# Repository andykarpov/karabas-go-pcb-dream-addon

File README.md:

# Karabas-Go rev.A SAM2695 addon

A small pcb to add midi functionality to Karabas-Go (and possibly other ZX Spectrum machines with AY chip).

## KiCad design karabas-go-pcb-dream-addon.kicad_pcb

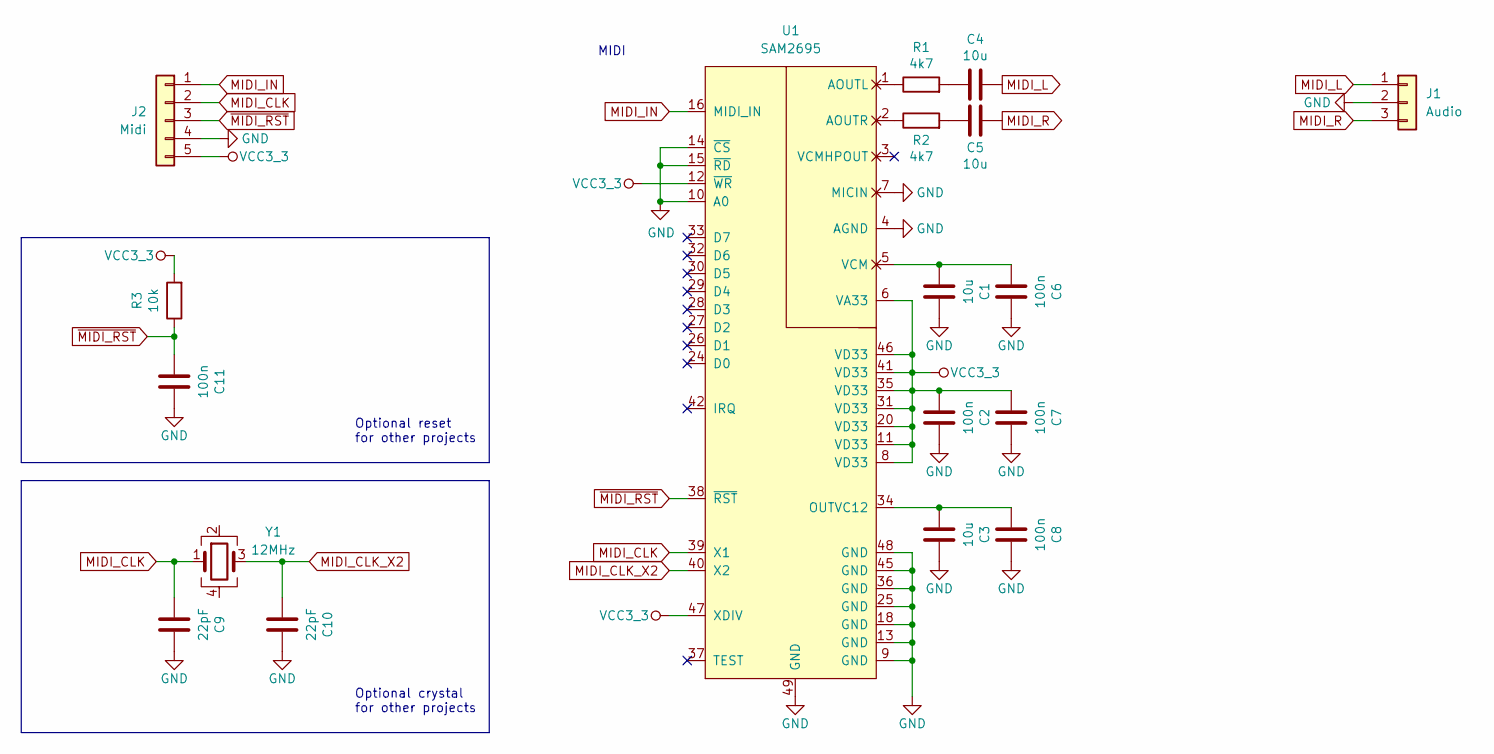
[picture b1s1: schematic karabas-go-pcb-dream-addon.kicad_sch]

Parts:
C1, C3, C4, C5: 10u; C_0603_1608Metric_Pad1.08x0.95mm_HandSolder
C2, C6, C7, C8, C11: 100n; C_0603_1608Metric_Pad1.08x0.95mm_HandSolder
C9, C10: 22pF; C_0603_1608Metric_Pad1.08x0.95mm_HandSolder
J1: Audio; PinHeader_1x03_P2.54mm_Vertical
J2: Midi; PinHeader_1x05_P2.54mm_Vertical
R1, R2: 4k7; R_0603_1608Metric_Pad0.98x0.95mm_HandSolder
R3: 10k; R_0603_1608Metric_Pad0.98x0.95mm_HandSolder
U1: SAM2695; QFN-48-1EP_6x6mm_P0.4mm_EP4.2x4.2mm
Y1: 12MHz; Crystal_SMD_3225-4Pin_3.2x2.5mm_HandSoldering

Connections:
GND: C1.2, C2.2, C3.2, C6.2, C7.2, C8.2, C9.2, C10.2, C11.2, J1.2, J2.4, U1.4 (AGND), U1.7 (MICIN), U1.9 (GND), U1.10 (A0), U1.13 (GND), U1.14 (~CS), U1.15 (~RD), U1.18 (GND), U1.25 (GND), U1.36 (GND), U1.45 (GND), U1.48 (GND), U1.49 (GND)
MIDI_CLK: C9.1, J2.2, U1.39 (X1), Y1.1
MIDI_CLK_X2: C10.1, U1.40 (X2), Y1.3
MIDI_IN: J2.1, U1.16 (MIDI_IN)
MIDI_L: C4.2, J1.1
MIDI_R: C5.2, J1.3
unnamed: C4.1, R1.2
unnamed: C5.1, R2.2
unnamed: R1.1, U1.1 (AOUTL)
unnamed: R2.1, U1.2 (AOUTR)
unnamed: C3.1, C8.1, U1.34 (OUTVC12)
unnamed: C1.1, C6.1, U1.5 (VCM)
VCC3_3: C2.1, C7.1, J2.5, R3.2, U1.6 (VA33), U1.8 (VD33), U1.11 (VD33), U1.12 (~WR), U1.20 (VD33), U1.31 (VD33), U1.35 (VD33), U1.41 (VD33), U1.46 (VD33), U1.47 (XDIV)
~MIDI_RST: C11.1, J2.3, R3.1, U1.38 (~RST)

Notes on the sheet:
MIDI
Optional reset for other projects
Optional crystal for other projects

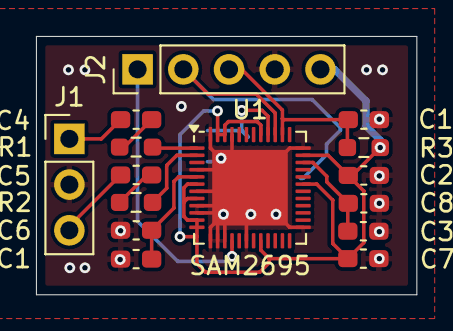
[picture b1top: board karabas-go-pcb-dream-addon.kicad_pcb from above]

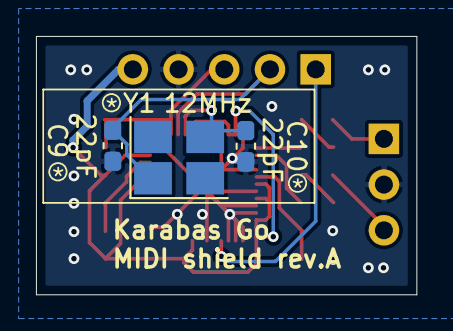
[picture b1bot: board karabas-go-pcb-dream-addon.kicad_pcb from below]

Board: 2 copper layers, 21.1 x 14.4 mm, 18 parts (3 on the bottom side), 14 nets.
